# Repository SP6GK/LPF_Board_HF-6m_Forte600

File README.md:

# LPF_Board_HF-6m_Forte600
Design of a LPF board with 6 filters covering entire HF spectrum and 6 m band. Suitable for 600 W (or more) LDMOS/BJT amplifiers.

## Overview

For a detailed theory of operation and a description of the design process, you can read section 2.2.3 of my thesis: [Optimization of HF Amplifier TLT Forte600 Documentation](https://github.com/SP6GK/Forte-600-HF-RF-Amplifier/blob/main/Optimization_HF_amplifier_TLT_Forte600Documentation.pdf).

This low pass filter board was designed for a 600 W amplifier and successfully withstood 600 W of CW power with no issues. It is overrated to handle about 1 kW, however, in such case, the size of some of the toroids should be increased.  
These filters used in the Forte 600 ([Forte 600 project repo](https://github.com/SP6GK/Forte-600-HF-RF-Amplifier)) provide a worst-case harmonic suppression of 54 dBc for the 15 m band. Check the `/Results` directory for S21 and S11 measurements, or refer to sections 4.7 and 4.8 of my thesis for a more in-depth discussion of the results: [Optimization of HF Amplifier TLT Forte600 Documentation](https://github.com/SP6GK/Forte-600-HF-RF-Amplifier/blob/main/Optimization_HF_amplifier_TLT_Forte600Documentation.pdf).  
During assembly use only high quality, high current capable, COG capacitors rated at 1 kV or more.

The board includes a tandem match coupler, allowing the forward and reflected power at the output to be measured. The desired LPF is selected either by applying a low level 5 V signal to connector J4, which requires 7 wires, or by driving a shift register (U2) directly from a microcontroller (3.3 V to 5 V) using only 3 wires.  
The code for band changing and shift register driving is available in my repository for the LDMOS amplifier controller: [Link](https://github.com/SP6GK/RF_Power_Amplifier_Controller_V1).  
To find out more about the Forte 600 project, you can visit my website: [www.sp6gk.com](https://www.sp6gk.com/).

## Directory Structure

- **/bom**  
  Contains an interactive HTML BOM for assembly and the `BOM_LC.ods` spreadsheet, which indicates the number of turns and suggested values for capacitors, ensuring that the combined capacitance value is achieved using at least 4 parallel capacitors.

- **/Gerbers**  
  Files for sending the project to your favorite PCB fabricator.

- **/KiCad**  
  Contains the PCB project files.

- **/PDF**  
  Contains 1:1 scale prints of the copper and silk screen layers.

- **/Results**  
  Contains S21 and S11 measurements of the assembled board. Measurements were made using a calibrated LiteVNA 64, and .s2p files were plotted in AWR Designer.

- **Coilformer1y.stl** & **Coilformer2.stl**  
  Temporary coil formers for the 6m band, which you can 3D print and then wind the coil on.

- **LPF.asc**  
  LTspice simulation of the LPF filters.

- **LPF+6m_Schematic.pdf**  
  schematic document.

- **LPF_live.mlx**  
  A MATLAB Live Script for the calculation of LC elements, formulas and values for polynomials were sourced from "Experimental Methods in RF Design" book.

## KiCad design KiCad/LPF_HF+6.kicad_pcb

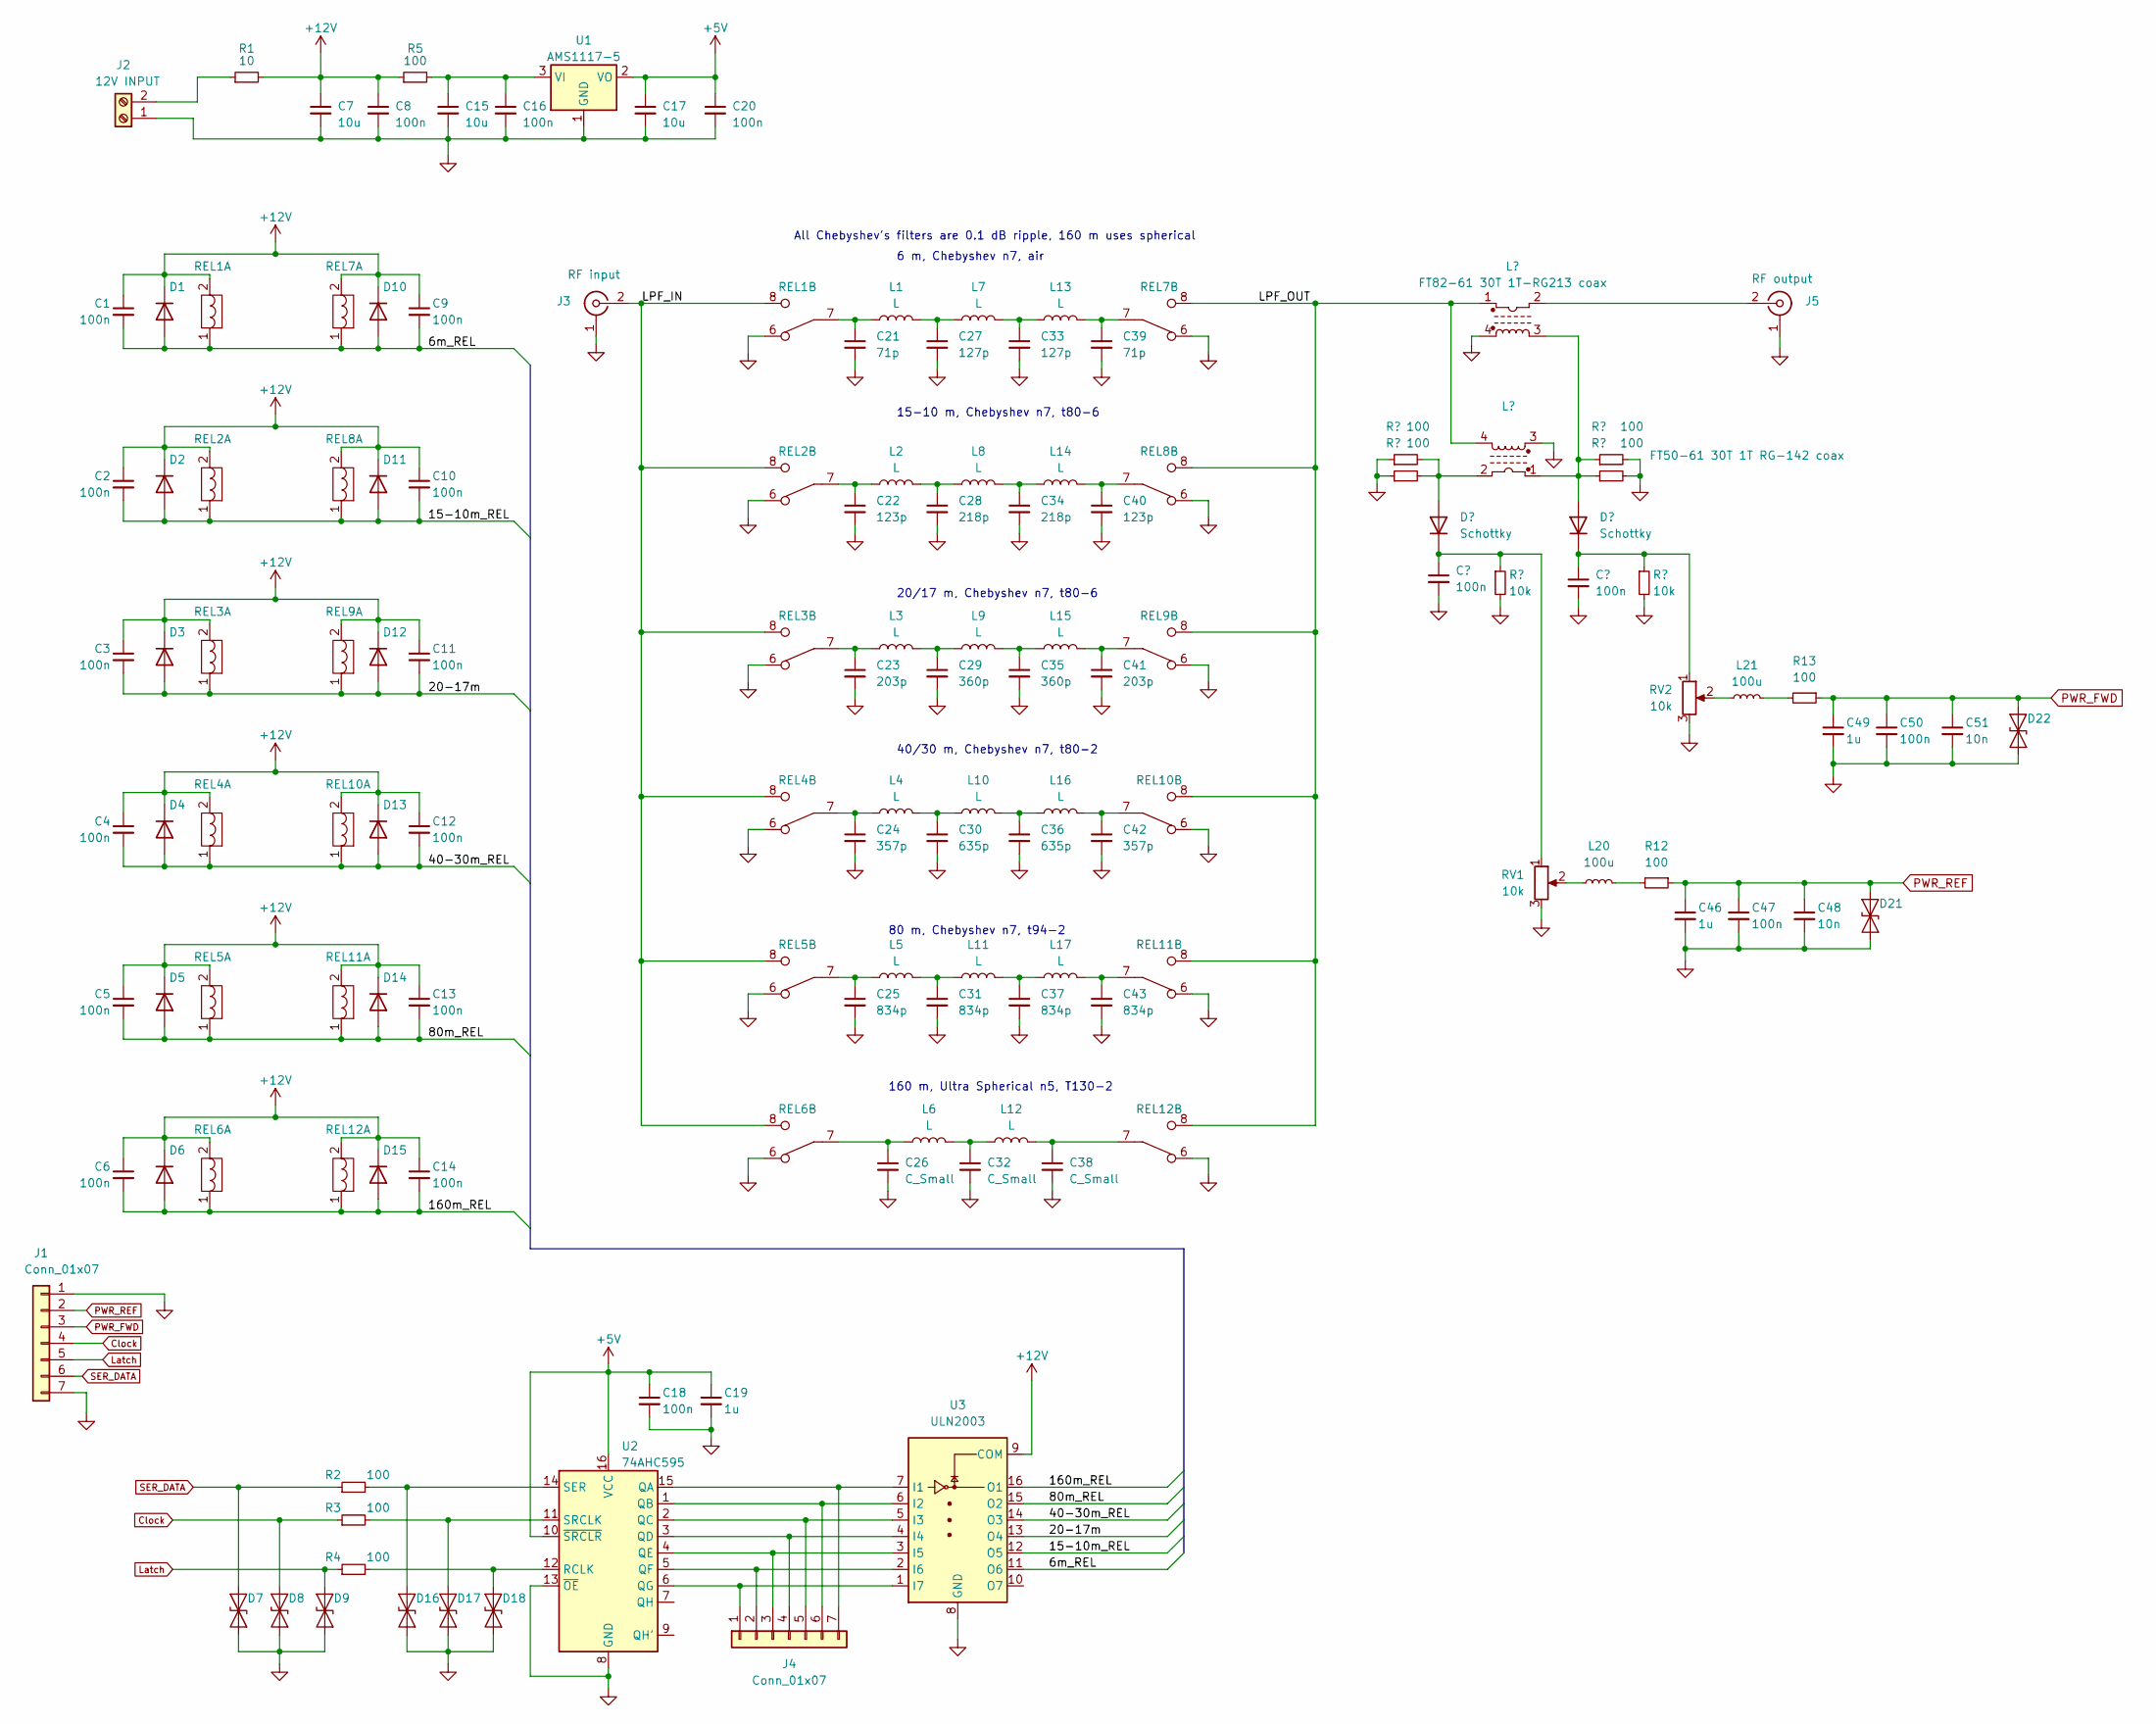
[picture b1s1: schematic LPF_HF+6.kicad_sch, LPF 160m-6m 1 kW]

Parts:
C1, C2, C3, C4, C5, C6, C8, C9, C10, C11, C12, C13, C14, C16, C18, C20, C44, C45, C47, C50: 100n; C_0603_1608Metric_Pad1.08x0.95mm_HandSolder
C7, C17: 10u; C_1206_3216Metric_Pad1.33x1.80mm_HandSolder
C15: 10u; C_1206_3216Metric
C19, C46, C49: 1u; C_0603_1608Metric_Pad1.08x0.95mm_HandSolder
C21, C39: 71p; 4x1206_2
C22, C40: 123p; 4x1206_2
C23, C41: 203p; 4x1206_2
C24, C42: 357p; 4x1206_2
C25, C31, C37, C43: 834p; 4x1206_2
C26, C32, C38: C_Small; 6x1206
C27, C33: 127p; 4x1206_2
C28, C34: 218p; 4x1206_2
C29, C35: 360p; 4x1206_2
C30, C36: 635p; 4x1206_2
C48, C51: 10n; C_0603_1608Metric_Pad1.08x0.95mm_HandSolder
D1, D2, D3, D4, D5, D6, D10, D11, D12, D13, D14, D15: 1N4007; D_SMA
D7, D8, D9, D16, D17, D18, D21, D22: SD12_SOD323; D_SOD-323
D19, D20: Schottky; D_SMA
J1, J4: Conn_01x07; JST_EH_B7B-EH-A_1x07_P2.50mm_Vertical
J2: 12V INPUT; TerminalBlock_bornier-2_P5.08mm
J3: RF input; Coax_Mount
J5: RF output; Coax_Mount
L1, L2, L3, L4, L5, L7, L8, L9, L10, L11, L13, L14, L15, L16, L17: L; T94-Inductor
L6, L12: L; T106-Inductor
L18: FT50-61 30T 1T RG-142 coax; T94-SWR_TRAFO
L19: FT82-61 30T 1T-RG213 coax; T94-SWR_TRAFO
L20, L21: 100u; L_0805_2012Metric_Pad1.05x1.20mm_HandSolder
R1: 10; R_1206_3216Metric_Pad1.30x1.75mm_HandSolder
R2, R3, R4, R5, R12, R13: 100; R_0603_1608Metric_Pad0.98x0.95mm_HandSolder
R6, R7, R9, R10: 100; R_2010_5025Metric_Pad1.40x2.65mm_HandSolder
R8, R11: 10k; R_0603_1608Metric_Pad0.98x0.95mm_HandSolder
REL1, REL2, REL3, REL4, REL5, REL6, REL7, REL8, REL9, REL10, REL11, REL12: RM85; RM85_Relay
RV1, RV2: 10k; Potentiometer_Bourns_3266Y_Vertical
U1: AMS1117-5; SOT-223-3_TabPin2
U2: 74AHC595; SO-16_3.9x9.9mm_P1.27mm
U3: ULN2003; SO-16_3.9x9.9mm_P1.27mm

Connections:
+12V: C1.1, C2.1, C3.1, C4.1, C5.1, C6.1, C7.1, C8.1, C9.1, C10.1, C11.1, C12.1, C13.1, C14.1, D1.1 (K), D2.1 (K), D3.1 (K), D4.1 (K), D5.1 (K), D6.1 (K), D10.1 (K), D11.1 (K), D12.1 (K), D13.1 (K), D14.1 (K), D15.1 (K), R1.2, R5.1, REL1.2, REL2.2, REL3.2, REL4.2, REL5.2, REL6.2, REL7.2, REL8.2, REL9.2, REL10.2, REL11.2, REL12.2, U3.9 (COM)
/6m_REL: C1.2, C9.2, D1.2 (A), D10.2 (A), REL1.1, REL7.1, U3.11 (O6)
/15-10m_REL: C2.2, C10.2, D2.2 (A), D11.2 (A), REL2.1, REL8.1, U3.12 (O5)
/20-17m: C3.2, C11.2, D3.2 (A), D12.2 (A), REL3.1, REL9.1, U3.13 (O4)
/40-30m_REL: C4.2, C12.2, D4.2 (A), D13.2 (A), REL4.1, REL10.1, U3.14 (O3)
/80m_REL: C5.2, C13.2, D5.2 (A), D14.2 (A), REL5.1, REL11.1, U3.15 (O2)
/160m_REL: C6.2, C14.2, D6.2 (A), D15.2 (A), REL6.1, REL12.1, U3.16 (O1)
/LPF_IN: J3.2 (In), REL1.5, REL1.8, REL2.5, REL2.8, REL3.5, REL3.8, REL4.5, REL4.8, REL5.5, REL5.8, REL6.5, REL6.8
/LPF_OUT: L18.4, L19.1, REL7.5, REL7.8, REL8.5, REL8.8, REL9.5, REL9.8, REL10.5, REL10.8, REL11.5, REL11.8, REL12.5, REL12.8
Clock: D8.1 (A1), J1.4, R3.1
GND: C7.2, C8.2, C15.2, C16.2, C17.2, C18.2, C19.2, C20.2, C21.2, C22.2, C23.2, C24.2, C25.2, C26.2, C27.2, C28.2, C29.2, C30.2, C31.2, C32.2, C33.2, C34.2, C35.2, C36.2, C37.2, C38.2, C39.2, C40.2, C41.2, C42.2, C43.2, C44.2, C45.2, C46.2, C47.2, C48.2, C49.2, C50.2, C51.2, D7.2 (A2), D8.2 (A2), D9.2 (A2), D16.2 (A2), D17.2 (A2), D18.2 (A2), D21.2 (A2), D22.2 (A2), J1.1, J1.7, J2.1, J3.1 (Ext), J5.1 (Ext), L18.3, L19.4, R6.1, R7.1, R8.2, R9.2, R10.2, R11.2, REL1.3, REL1.6, REL2.3, REL2.6, REL3.3, REL3.6, REL4.3, REL4.6, REL5.3, REL5.6, REL6.3, REL6.6, REL7.3, REL7.6, REL8.3, REL8.6, REL9.3, REL9.6, REL10.3, REL10.6, REL11.3, REL11.6, REL12.3, REL12.6, RV1.3, RV2.3, U1.1 (GND), U2.8 (GND), U2.13 (~OE), U3.8 (GND); also elsewhere on the board
Latch: D9.1 (A1), J1.5, R4.1
unnamed: C21.1, L1.1, REL1.4, REL1.7
unnamed: C22.1, L2.1, REL2.4, REL2.7
unnamed: C23.1, L3.1, REL3.4, REL3.7
unnamed: C24.1, L4.1, REL4.4, REL4.7
unnamed: C25.1, L5.1, REL5.4, REL5.7
unnamed: C26.1, L6.1, REL6.4, REL6.7
unnamed: C27.1, L1.2, L7.1
unnamed: C28.1, L2.2, L8.1
unnamed: C29.1, L3.2, L9.1
unnamed: C30.1, L4.2, L10.1
unnamed: C31.1, L5.2, L11.1
unnamed: C32.1, L6.2, L12.1
unnamed: C33.1, L7.2, L13.1
unnamed: C34.1, L8.2, L14.1
unnamed: C35.1, L9.2, L15.1
unnamed: C36.1, L10.2, L16.1
unnamed: C37.1, L11.2, L17.1
unnamed: C38.1, L12.2, REL12.4, REL12.7
unnamed: C40.1, L14.2, REL8.4, REL8.7
unnamed: C41.1, L15.2, REL9.4, REL9.7
unnamed: C42.1, L16.2, REL10.4, REL10.7
unnamed: C43.1, L17.2, REL11.4, REL11.7
unnamed: D16.1 (A1), R2.2, U2.14 (SER)
unnamed: D17.1 (A1), R3.2, U2.11 (SRCLK)
unnamed: D18.1 (A1), R4.2, U2.12 (RCLK)
unnamed: D19.2 (A), L18.2, R6.2, R7.2
unnamed: C44.1, D19.1 (K), R8.1, RV1.1
unnamed: D20.2 (A), L18.1, L19.3, R9.1, R10.1
unnamed: C45.1, D20.1 (K), R11.1, RV2.1
unnamed: J2.2, R1.1
unnamed: J4.1, U2.6 (QG), U3.1 (I7)
unnamed: J4.2, U2.5 (QF), U3.2 (I6)
unnamed: J4.3, U2.4 (QE), U3.3 (I5)
unnamed: J4.4, U2.3 (QD), U3.4 (I4)
unnamed: J4.5, U2.2 (QC), U3.5 (I3)
unnamed: J4.6, U2.1 (QB), U3.6 (I2)
unnamed: J4.7, U2.15 (QA), U3.7 (I1)
unnamed: J5.2 (In), L19.2
unnamed: L20.1, RV1.2
unnamed: L20.2, R12.2
unnamed: L21.1, RV2.2
unnamed: L21.2, R13.2
unnamed: C15.1, C16.1, R5.2, U1.3 (VI)
PWR_FWD: C49.1, C50.1, C51.1, D22.1 (A1), J1.3, R13.1
PWR_REF: C46.1, C47.1, C48.1, D21.1 (A1), J1.2, R12.1
SER_DATA: D7.1 (A1), J1.6, R2.1

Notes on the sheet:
15-10 m, Chebyshev n7, t80-6
6 m, Chebyshev n7, air
All Chebyshev's filters are 0.1 dB ripple, 160 m uses spherical
20/17 m, Chebyshev n7, t80-6
80 m, Chebyshev n7, t94-2
40/30 m, Chebyshev n7, t80-2
160 m, Ultra Spherical n5, T130-2

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
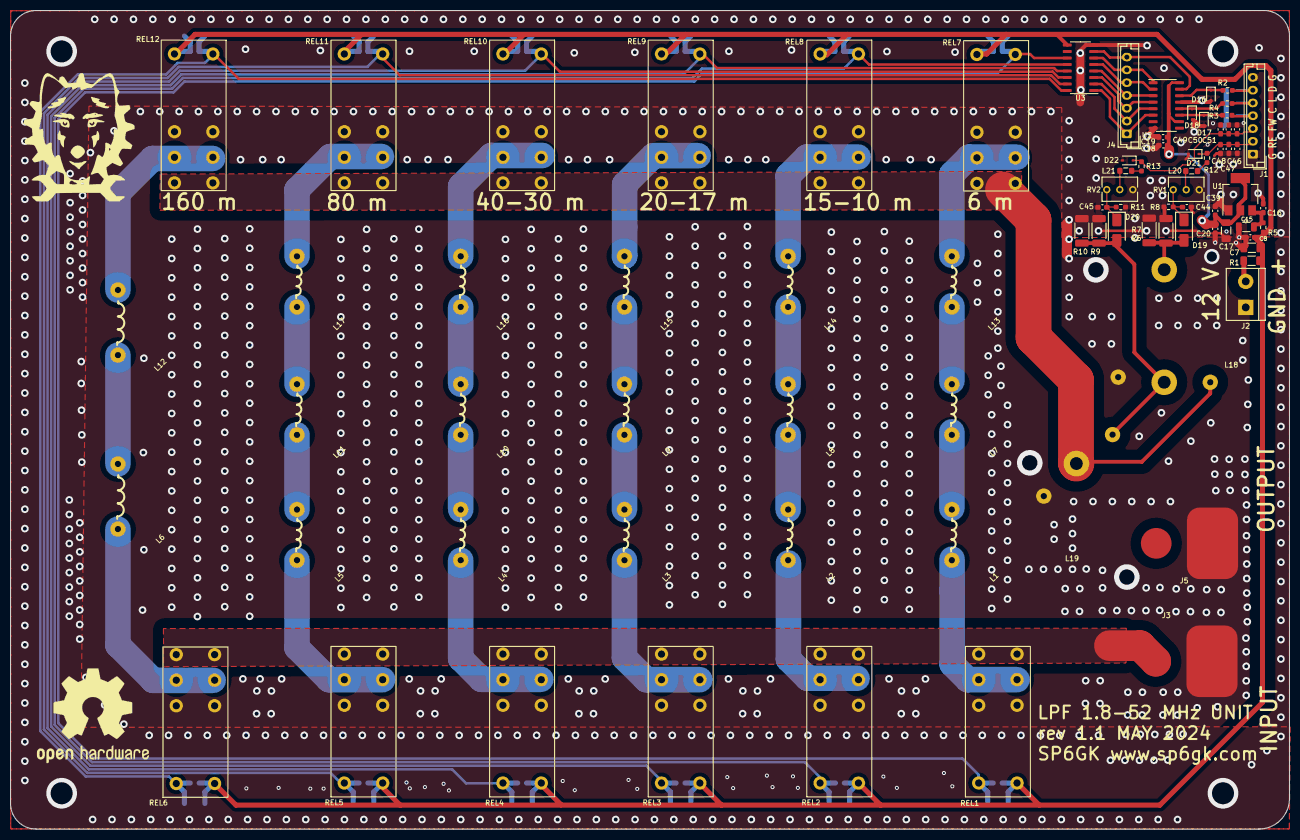
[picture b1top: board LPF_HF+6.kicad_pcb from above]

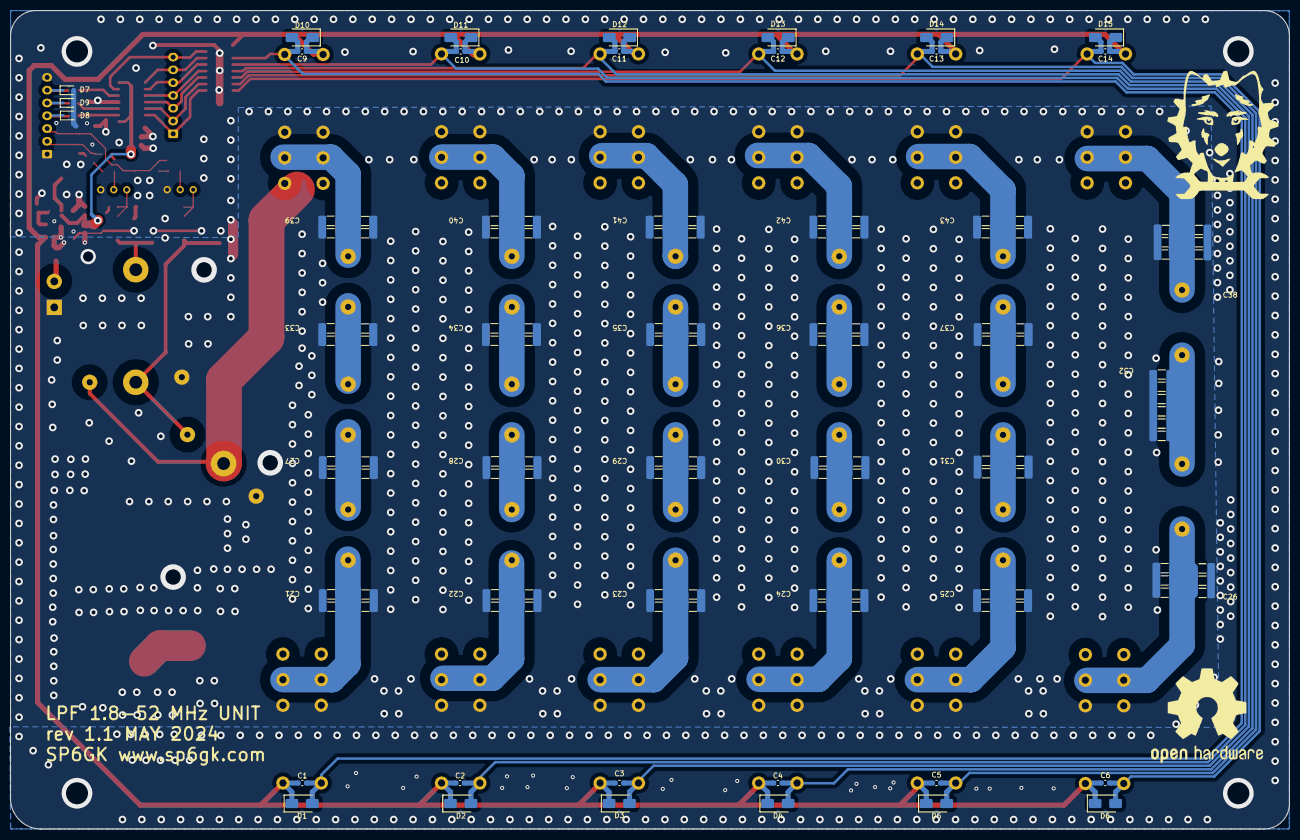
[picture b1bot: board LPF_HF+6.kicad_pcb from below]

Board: 2 copper layers, 250.0 x 160.0 mm, 130 parts (50 on the bottom side), 60 nets.

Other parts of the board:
C39#2: 71p; 4x1206_2

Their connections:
GND: C39#2.2; also elsewhere on the board

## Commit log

2024-08-27 Create LICENSE
2024-08-28 Add files via upload
    Updated KiCad project
